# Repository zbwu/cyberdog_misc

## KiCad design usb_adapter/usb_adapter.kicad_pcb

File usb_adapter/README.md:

# Cyberdog USB Adapter

Demultiplexing "Download" Type-C port to Console, Recovery USB and Recovery Button

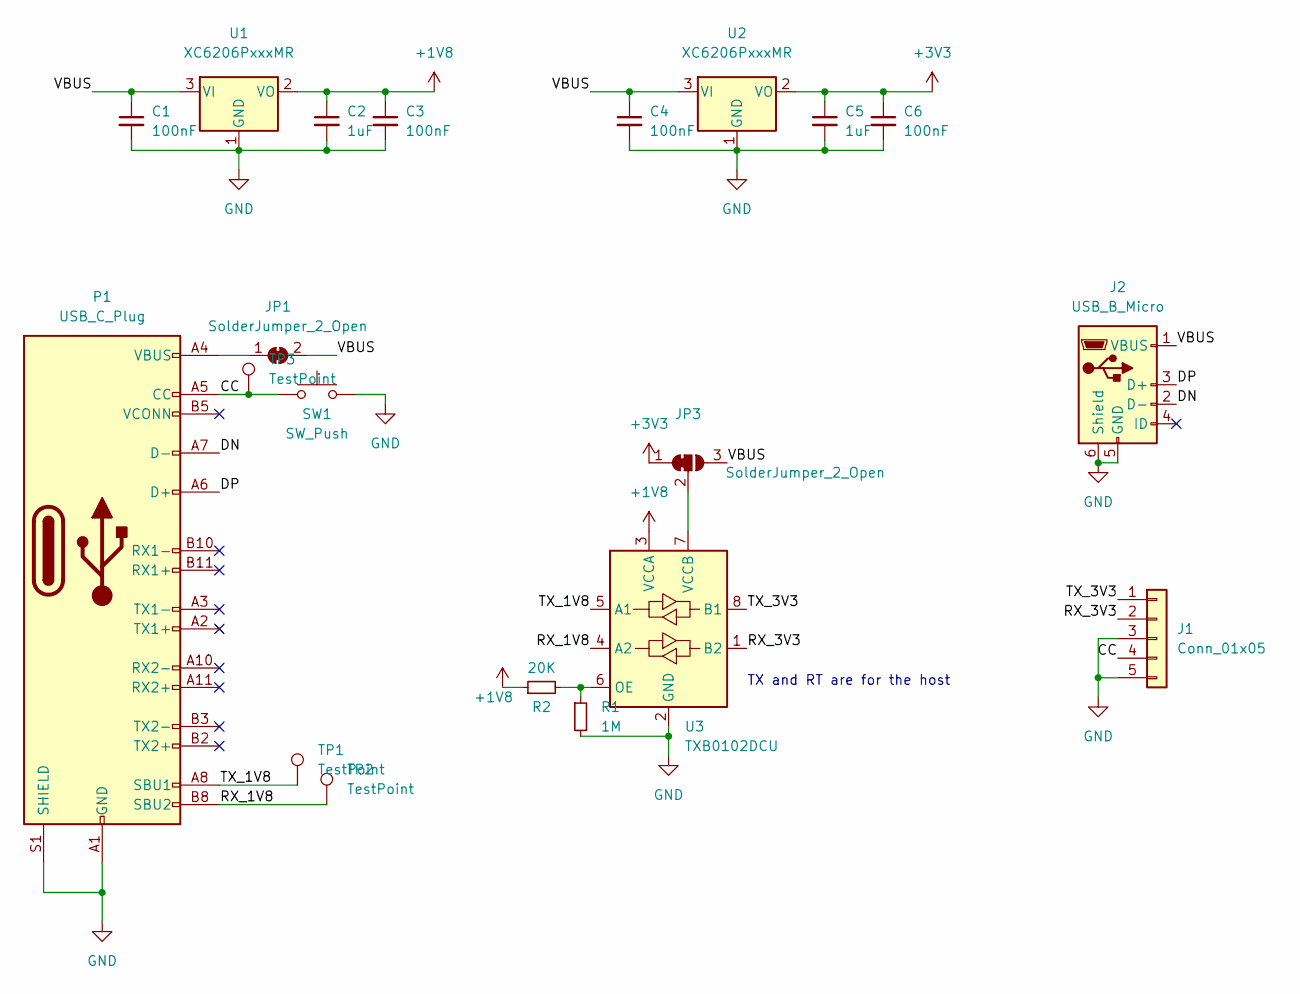
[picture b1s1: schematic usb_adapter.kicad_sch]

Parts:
C1, C3, C4, C6: 100nF; C_0603_1608Metric_Pad1.08x0.95mm_HandSolder
C2, C5: 1uF; C_1206_3216Metric_Pad1.33x1.80mm_HandSolder
J1: Conn_01x05; Harwin_M20-89005xx_1x05_P2.54mm_Horizontal
J2: USB_B_Micro; USB_Micro-B_YourCee_7.2_16Pin
JP1: SolderJumper_2_Open; SolderJumper-2_P1.3mm_Bridged_RoundedPad1.0x1.5mm
JP3: SolderJumper_2_Open; SolderJumper-3_P1.3mm_Bridged12_RoundedPad1.0x1.5mm
P1: USB_C_Plug; TYPE-C-31-G-08
R1: 1M; R_0603_1608Metric_Pad0.98x0.95mm_HandSolder
R2: 20K; R_0603_1608Metric_Pad0.98x0.95mm_HandSolder
SW1: SW_Push; SW_SPST_CK_RS282G05A3
TP1, TP2, TP3: TestPoint; TestPoint_Pad_D1.5mm
U1, U2: XC6206PxxxMR; SOT-23
U3: TXB0102DCU; VSSOP-8_2.4x2.1mm_P0.5mm

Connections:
+1V8: C2.1, C3.1, R2.1, U1.2 (VO), U3.3 (VCCA)
+3V3: C5.1, C6.1, JP3.1 (A), U2.2 (VO)
/CC: J1.4, P1.A5 (CC), SW1.1, TP3.1
/DN: J2.2 (D-), P1.A7 (D-)
/DP: J2.3 (D+), P1.A6 (D+)
/RX_1V8: P1.B8 (SBU2), TP2.1, U3.4 (A2)
/RX_3V3: J1.2, U3.1 (B2)
/TX_1V8: P1.A8 (SBU1), TP1.1, U3.5 (A1)
/TX_3V3: J1.1, U3.8 (B1)
/VBUS: C1.1, C4.1, J2.1 (VBUS), JP1.2 (B), JP3.3 (B), U1.3 (VI), U2.3 (VI)
GND: C1.2, C2.2, C3.2, C4.2, C5.2, C6.2, J1.3, J1.5, J2.5 (GND), J2.6 (Shield), P1.A1 (GND), P1.A12 (GND), P1.B1 (GND), P1.B12 (GND), P1.S1 (SHIELD), R1.2, SW1.2, U1.1 (GND), U2.1 (GND), U3.2 (GND)
unnamed: JP1.1 (A), P1.A4 (VBUS), P1.A9 (VBUS), P1.B4 (VBUS), P1.B9 (VBUS)
unnamed: JP3.2 (C), U3.7 (VCCB)
unnamed: R1.1, R2.2, U3.6 (OE)

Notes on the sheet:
TX and RT are for the host

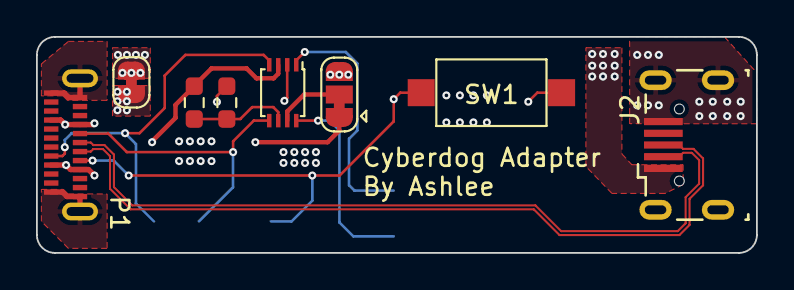
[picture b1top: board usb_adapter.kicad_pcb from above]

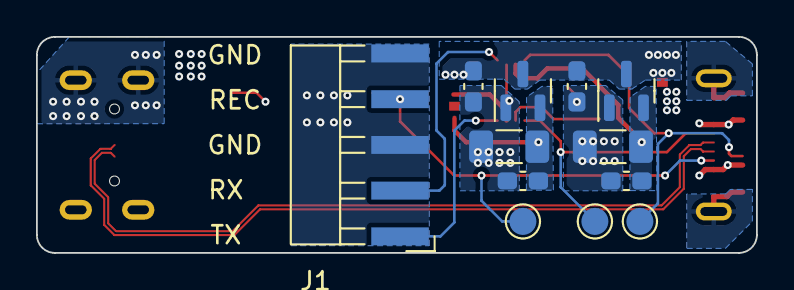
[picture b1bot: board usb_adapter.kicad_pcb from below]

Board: 4 copper layers, 40.0 x 12.0 mm, 20 parts (12 on the bottom side), 14 nets.

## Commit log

2021-11-09 add mcu protocol example, version 0.1
2021-11-09 add robot parameters, version 0.1
2022-04-16 Add an example of calling SpiHandler via dynamic loading
2022-04-16 Add BMS example
2022-04-17 Add Cyberdog usb_adapter
